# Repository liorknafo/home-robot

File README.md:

# R1 home robot

A round (Ø 318 mm, 135.15 mm tall) differential-drive home robot built around an NVIDIA Jetson Nano, together with the Unreal
simulator and the Python autonomy stack it is developed against.

| Folder | What's in it |
|---|---|
| [`home-robot-r1/`](home-robot-r1) | Robot hardware: parametric CAD (CadQuery), printable parts, the 4-layer power & I/O board (KiCad, generated from Python and auto-routed), fab package for JLCPCB, harness and BOM, bring-up guide |
| [`home-robot-sim/`](home-robot-sim) | Unreal Engine 5.8 simulator (a furnished apartment, the robot with its LiDAR, camera, IMU, encoders, bumpers and cliff sensors) and the autonomy controller (LiDAR mapping, camera low-obstacle detection, exploration, go-to) |

Status: work in progress. Nothing has been ordered or printed yet.

## Robot at a glance

- **Compute:** Jetson Nano 4 GB developer kit on standoffs over the motors: B01 (the CAD model) or A02 (same footprint, ports and power).
- **Board:** a 74 × 100 mm 4-layer power & I/O board under the Jetson. It carries:
  - a Raspberry Pi Pico for real-time I/O;
  - two Pololu DRV8874 motor drivers;
  - a GY-521 (MPU-6050) IMU;
  - fuses, a relay and connectors.
- **Sensors:**
  - an LDROBOT LD14 (D200) 2D LiDAR at 127.5 mm;
  - one camera at 80 mm;
  - four downward ToF cliff sensors;
  - a front bumper.
- **Drive:** Pololu 25D 99:1 encoder gearmotors.

## Key documents

**Hardware:**
- [`home-robot-r1/BRINGUP.md`](home-robot-r1/BRINGUP.md): assembly order and first power-up.
  - **J1 pin 1 is GND.**
  - Includes the IMU calibration.
- [`home-robot-r1/pcb/fab/ORDERING.md`](home-robot-r1/pcb/fab/ORDERING.md): exact JLCPCB order settings and a verify-before-ordering checklist.
- [`home-robot-r1/pcb/fab/`](home-robot-r1/pcb/fab): Gerbers, drill files, BOM, placement file, 1:1 PDF and board STEP.
- `home-robot-r1/parts-and-connections.json` and `cable-cut-list.json`: the BOM and the harness.

**Design history:** [`home-robot-sim/docs/superpowers/`](home-robot-sim/docs/superpowers) holds the specs and plans.

## What is not in this repo

- **Manufacturer 3D models:** NVIDIA Jetson Nano, Pololu motor and driver, Raspberry Pi Pico, LDROBOT LD14.
  - Their licences don't clearly allow redistribution, so they are fetched instead.
  - The same goes for the generated meshes that contain their geometry: `cad/assembly-meshes.json`, `cad/home-robot-r1.glb`, `design-review.html`, and the simulator's `Content/RobotData/assembly-meshes.json`.
  - Sources and checksums are in [`home-robot-r1/reference-models/SOURCE.txt`](home-robot-r1/reference-models/SOURCE.txt).
- **Simulator data:** recordings (`Saved/`), build output, caches and benchmark reports.

## Build

1. **Fetch the reference models:** `tools/fetch_reference_models.sh`. The NVIDIA Jetson model needs a manual download; the script prints the steps.
2. **Robot CAD:**
   - Python 3.13 with CadQuery 2.6.1 (`home-robot-r1/cad/requirements.txt`; CadQuery 2.8.0 + cadquery-ocp 7.9.3.1.1 on Python 3.14 also verified).
   - Run `python home-robot-r1/cad/build_robot.py`. It takes about 25 min, and writes the meshes, STEP, print STLs and validation report.
3. **Board (optional):**
   - KiCad 9.0.x (its bundled Python, `$KPY` in the script headers, runs the `pcb/` scripts and `ktest_*` tests): on macOS
     `/Applications/KiCad/KiCad.app/Contents/Frameworks/Python.framework/Versions/Current/bin/python3`, on Windows
     `C:\Program Files\KiCad\9.0\bin\python.exe` (or `%LOCALAPPDATA%\Programs\KiCad\9.0\bin\python.exe` for a per-user install), on
     Linux the system `python3` with the distribution's KiCad 9 packages.
   - Re-routing needs Java 25 and Freerouting 2.4.1 at `home-robot-r1/pcb/tools/freerouting.jar`. It isn't redistributed; download it from the Freerouting releases
     (`pcb/tools.py` pins its sha256, `FREEROUTING_SHA256`).
   - `pcb/tools.py` finds these per OS. Override any of them with `KICAD_CLI`, `KICAD_PYTHON`, `KICAD9_SYMBOL_DIR`, `KICAD9_FOOTPRINT_DIR`,
     `KICAD9_3DMODEL_DIR`, `JAVA` (or `JAVA_HOME`) and `FREEROUTING_JAR`.
   - `pcb/route.py` with no arguments reproduces the committed routing with these versions; it records them in the board's `ROUTED_WITH`.
   - KiCad 9.0.8's `kicad-cli`, on its first `sch erc` run in a fresh config dir, copies KiCad's template `fp-lib-table` into that dir and
     then crashes; every later run passes. So on a fresh install or CI the first `test_erc_has_no_errors` (or `test_schematic.py`) run
     fails: run it again, or first copy `<KiCad>/share/kicad/template/fp-lib-table` (macOS:
     `/Applications/KiCad/KiCad.app/Contents/SharedSupport/template/fp-lib-table`) to `fp-lib-table` in the 9.0 config dir
     (`%APPDATA%\kicad\9.0`, `~/Library/Preferences/kicad/9.0`, `~/.config/kicad/9.0`).
4. **Simulator:**
   - Unreal Engine 5.8 (macOS): build with `home-robot-sim/Scripts/build.command`.
   - Sync the robot data: `python home-robot-sim/Scripts/sync_robot_data.py`. It reads `../home-robot-r1/cad` and copies the robot meshes and parameters.
   - Launch with `Scripts/launch.command house polished`.
   - Start the autonomy service: `Scripts/start-autonomy.command`, then open http://127.0.0.1:8771/autonomy.html.
   - Python deps: `home-robot-sim/controller/requirements.txt`.
   - **Windows:** every `.command` script has a `.cmd` twin in `home-robot-sim/Scripts` (`build.cmd`, `launch.cmd house polished`,
     `start-autonomy.cmd`, `run-tests.cmd`, `drive-house.cmd`, `drive-square.cmd`, `process-cameras.cmd`).
     - One command runs everything: `.\home-robot-sim\Scripts\launch.cmd house polished` starts the simulator plus, in
       minimized windows, the autonomy service and object detection, then open http://127.0.0.1:8771/autonomy.html.
       Every launcher first stops its own earlier runs, so rerunning it never leaves duplicates (`NO_AUTONOMY=1` /
       `NO_VISION=1` skip a part).
     - Needs Unreal Engine 5.8 from the Epic Games Launcher (the scripts find it on any drive through the launcher's install record,
       or set `UE_ROOT`) and
       Visual Studio 2022 17.14+ with the "Game development with C++" workload, MSVC 14.38+ and Windows SDK 10.0.22621+.
     - The scripts make `home-robot-sim\.venv` on first use and run Python in UTF-8 mode (`PYTHONUTF8=1`). Set it yourself when you
       run the Python tools directly, e.g. the CAD build, or they read the UTF-8 sources in the ANSI code page.
     - `tools/fetch_reference_models.sh` runs in Git Bash. Verified with Python 3.13 + CadQuery 2.6.1 for the CAD build.
   - **Live object recognition (display only):** started by `launch.cmd`, or alone with `start-vision.cmd`. It runs
     YOLO26n-seg on each robot camera frame on the PC's NVIDIA GPU and shows boxes + masks under the dashboard's camera
     image. By default it runs a TensorRT engine for this PC's GPU, built on the fly the first time (about 1-2 minutes,
     `vision/ensure_engine.py`; the file name records the GPU and TensorRT version, so a new GPU or TensorRT gets a fresh
     build). It falls back to PyTorch when TensorRT is unavailable, or with `NO_TRT=1`.
     `start-vision.cmd --model <weights or .engine>` picks the model: any Ultralytics name (e.g. `yolo11n-seg.pt`), or
     `yolov12n-seg.pt`, fetched from the YOLOv12 authors' release and loaded through `vision/yolov12_compat.py`
     (Ultralytics publishes no YOLO12 segmentation weights). The robot does not act on these detections.
     The pipeline is PyTorch end to end (`vision/yoloseg`, no OpenCV) and is the same one the robot runs.
   - **On the Jetson Nano (TensorRT):** [`home-robot-sim/jetson/JETSON.md`](home-robot-sim/jetson/JETSON.md) goes step by step
     from the ONNX export on the PC to the FP16 engine and the live camera view on the Nano.
5. **Tests:**
   - Simulator: `cd home-robot-sim && python -m unittest discover -s tests`, plus `tests/scenarios_round.py`.
   - Robot pure tests: `cd home-robot-r1 && python -m unittest discover -s pcb/tests -t .` (or `python -m pytest pcb/tests`;
     they include the CAD review-page checks). The tests that need KiCad skip when it isn't found; `R1_REQUIRE_KICAD=1` makes them run (and fail).
   - Board tests in KiCad's Python: `cd home-robot-r1 && $KPY -m unittest pcb.tests.ktest_pcb pcb.tests.ktest_power pcb.tests.ktest_route`.

## Licence

MIT (see [`LICENSE`](LICENSE)) for everything in this repo: software, CAD, board design and documents. The manufacturer 3D models fetched by `tools/fetch_reference_models.sh` keep their own terms and are not part of this repo.

## Repository maintenance

This repo is a published snapshot of two working folders that live next to it. To refresh and push it:
`tools/sync.sh && git add -A && git commit -m "…" && git push`.

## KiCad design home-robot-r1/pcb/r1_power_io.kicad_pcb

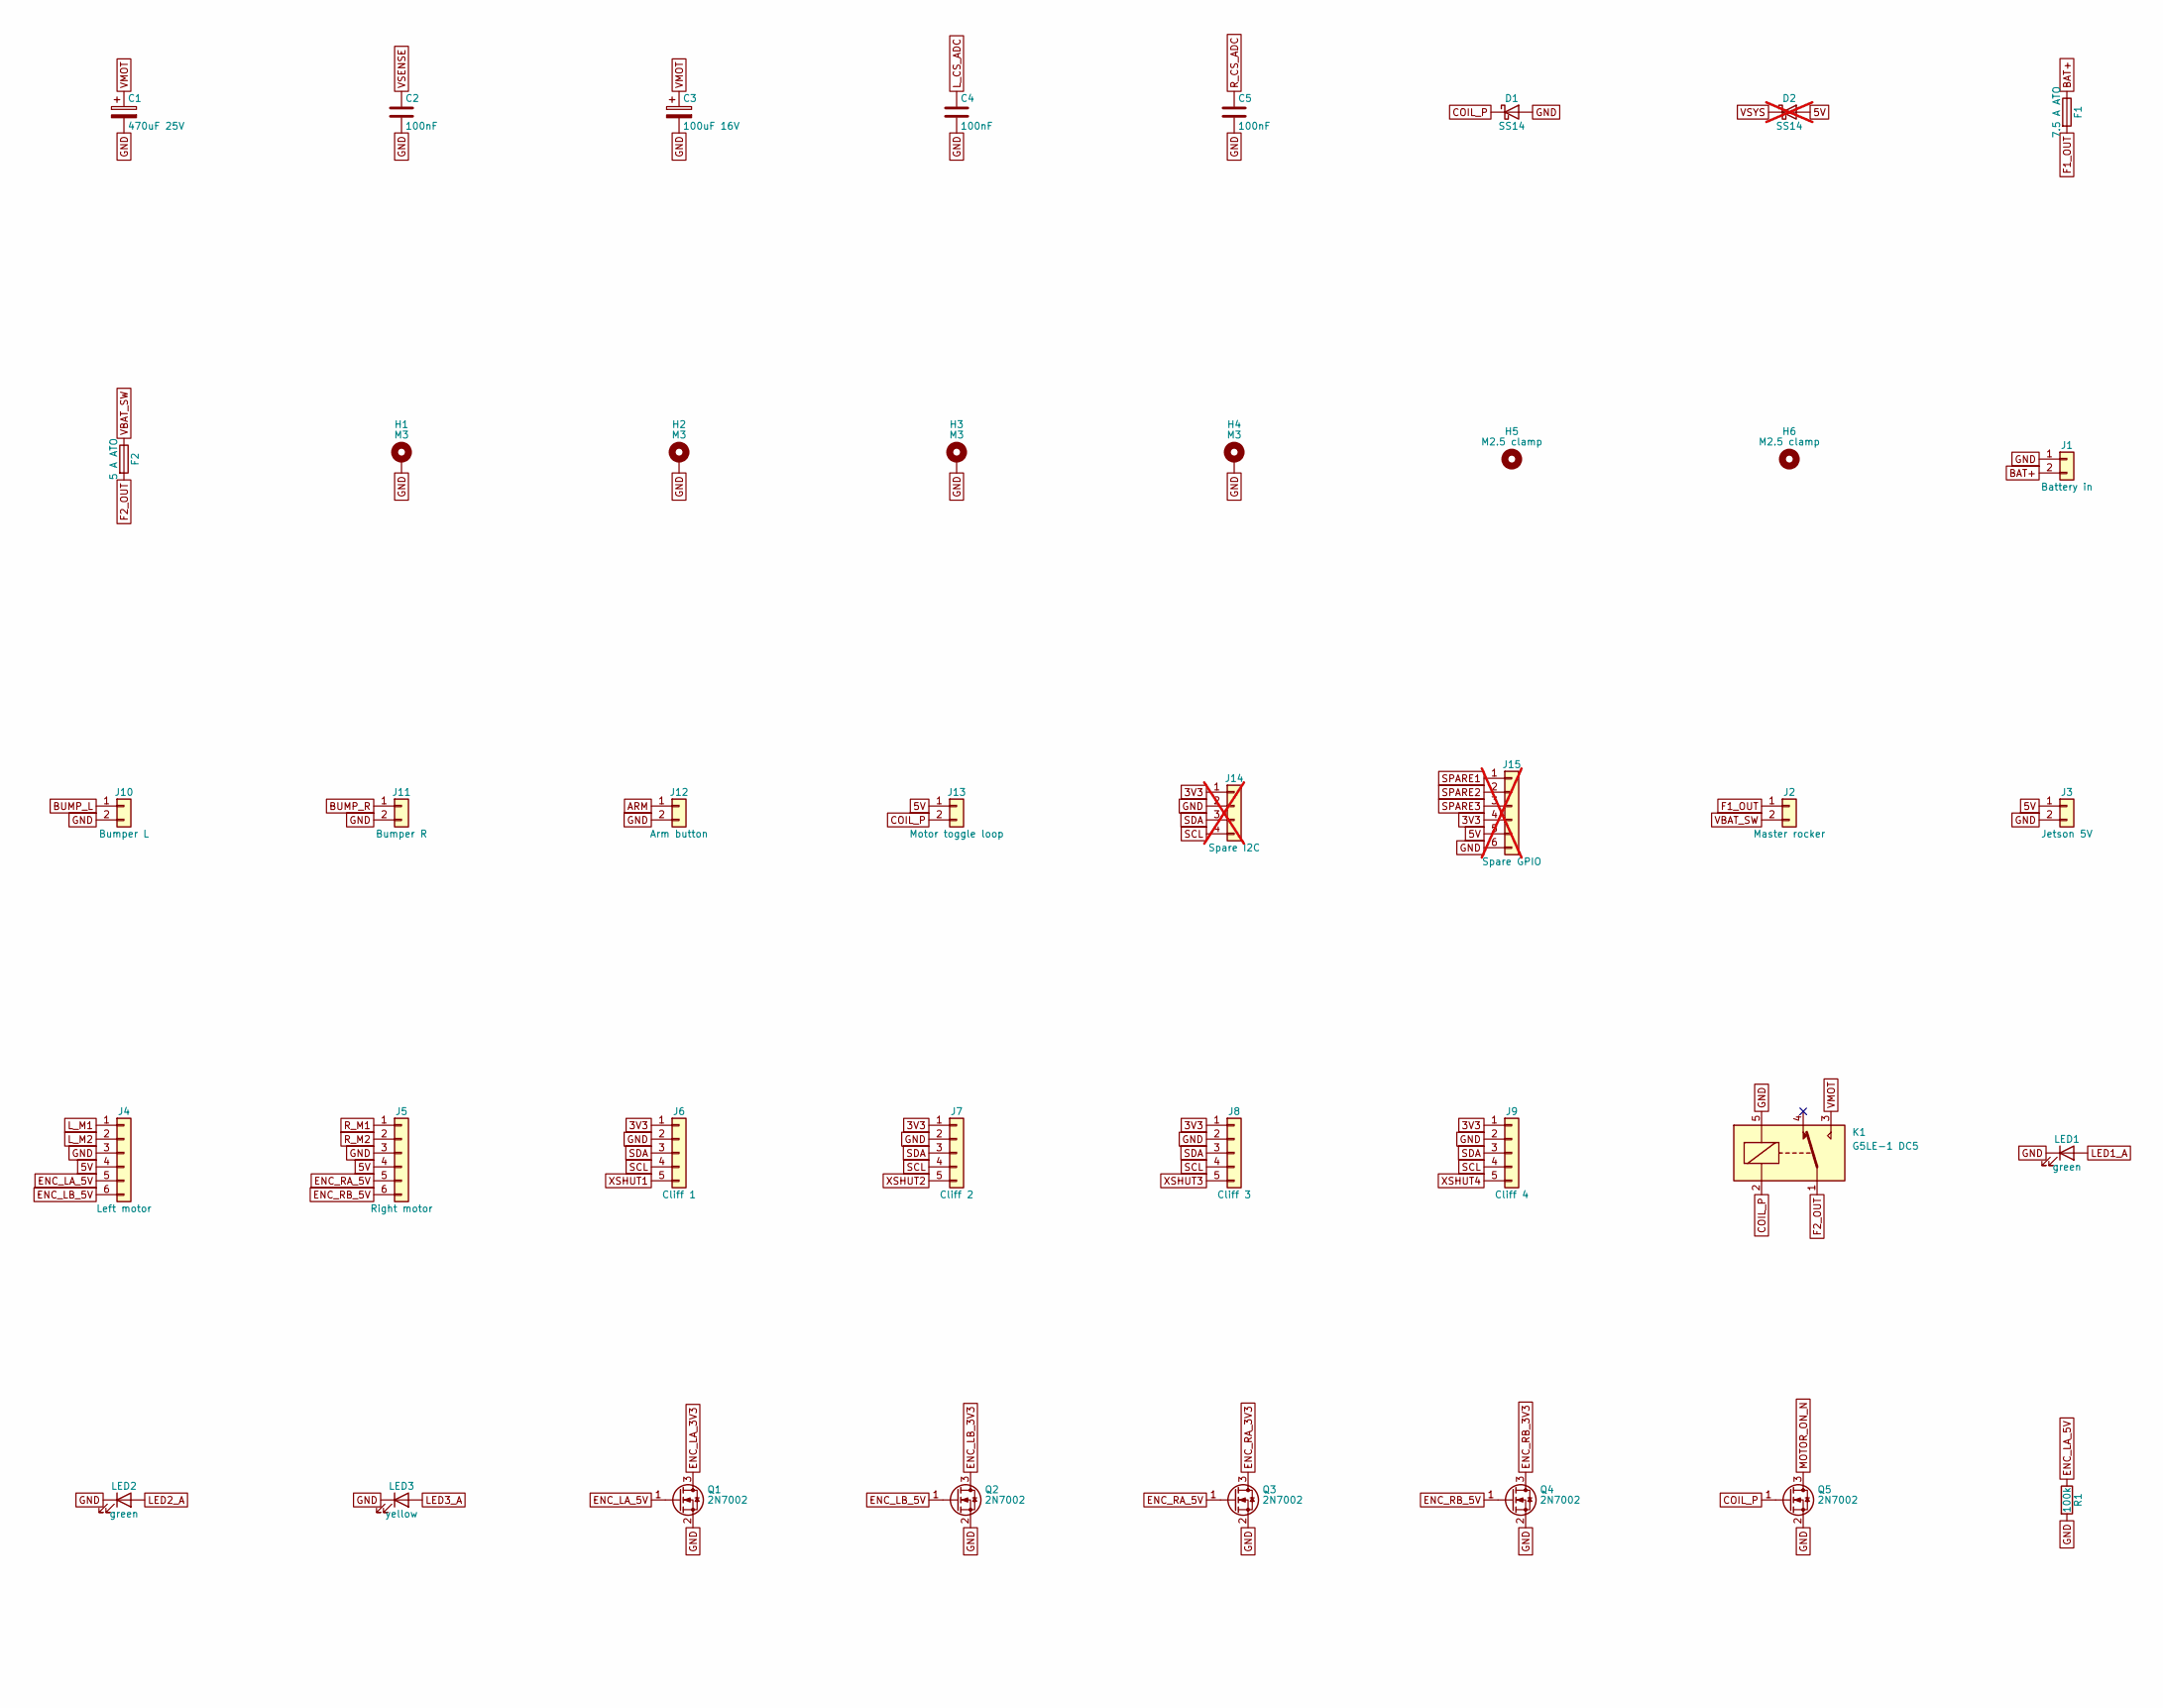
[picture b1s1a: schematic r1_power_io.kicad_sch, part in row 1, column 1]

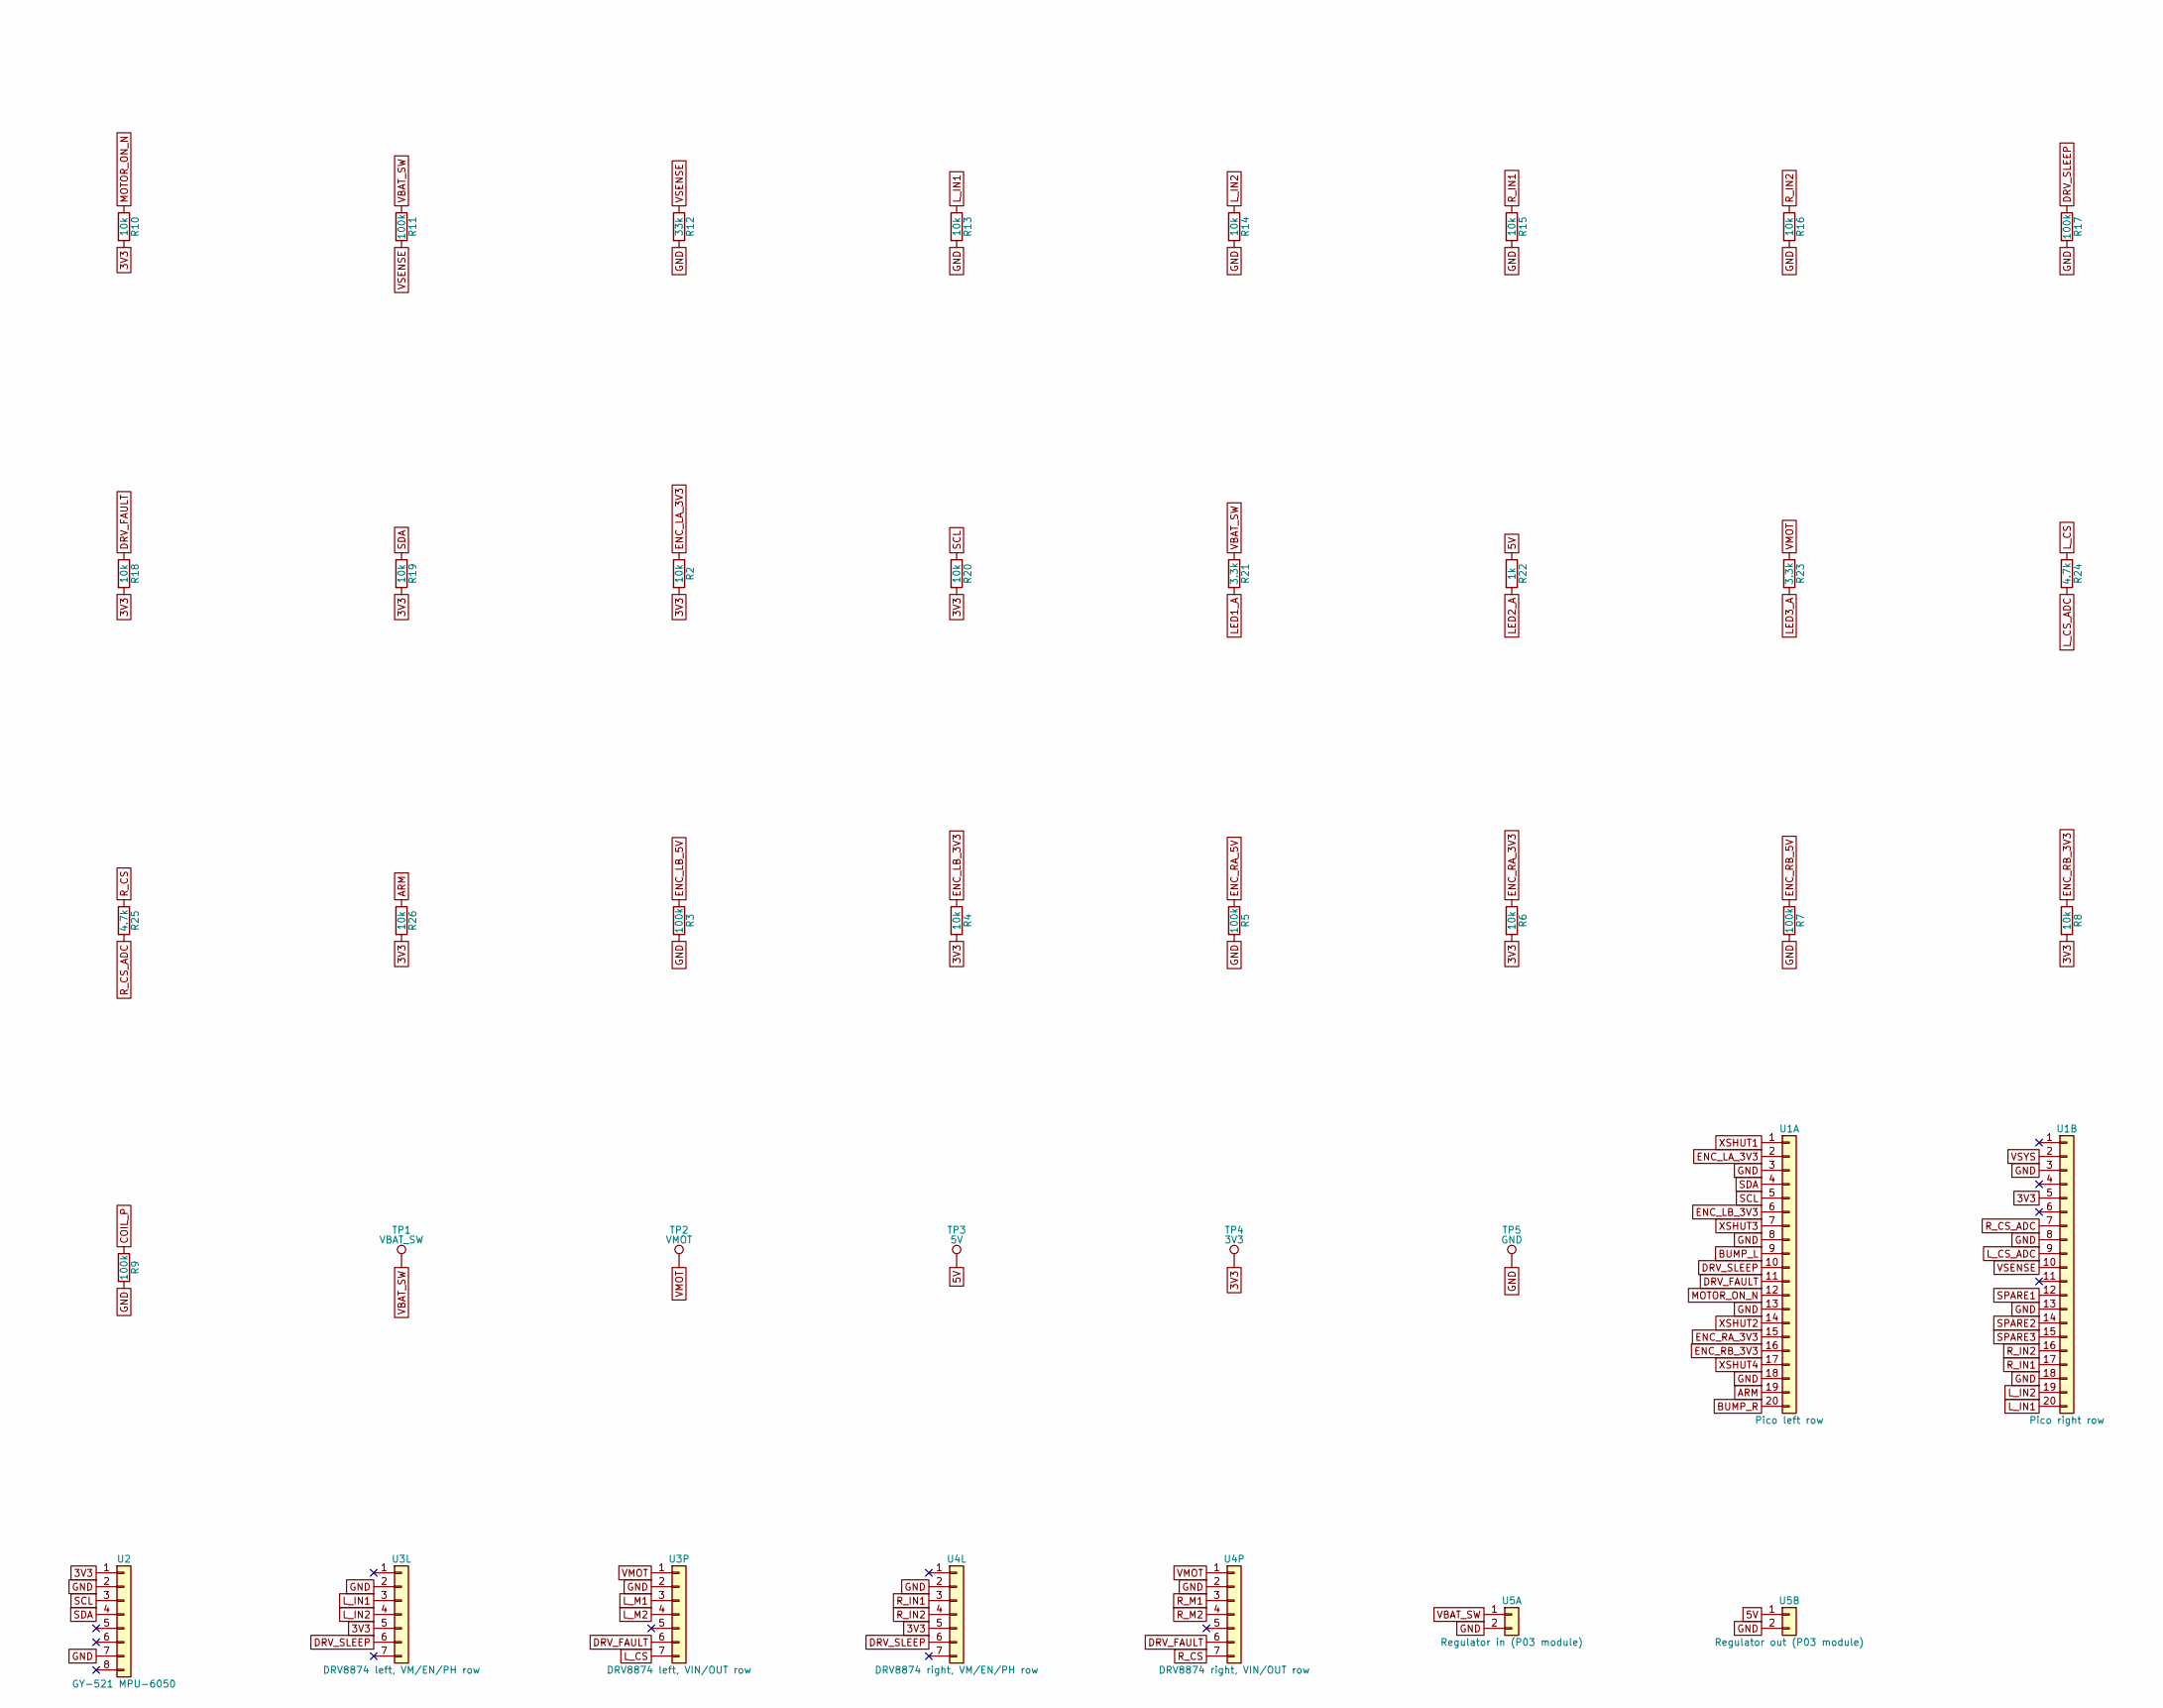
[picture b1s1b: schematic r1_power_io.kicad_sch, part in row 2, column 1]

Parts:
C1: 470uF 25V; CP_Radial_D10.0mm_P5.00mm
C2, C4, C5: 100nF; C_0805_2012Metric
C3: 100uF 16V; CP_Elec_6.3x5.8
D1: SS14; D_SMA
D2: SS14; D_SMA; not fitted
F1: 7.5 A ATO; FuseHolder_Blade_ATO_Littelfuse_FLR_178.6165
F2: 5 A ATO; FuseHolder_Blade_ATO_Littelfuse_FLR_178.6165
H1, H2, H3, H4: M3; MountingHole_3.2mm_M3_Pad_Via
H5, H6: M2.5 clamp; MountingHole_3mm
J1: Battery in; AMASS_XT30UPB-M_1x02_P5.0mm_Vertical
J2: Master rocker; JST_VH_B2P-VH_1x02_P3.96mm_Vertical
J3: Jetson 5V; Molex_Micro-Fit_3.0_43650-0200_1x02_P3.00mm_Horizontal
J4: Left motor; PinHeader_1x06_P2.54mm_Horizontal
J5: Right motor; PinHeader_1x06_P2.54mm_Horizontal
J6: Cliff 1; JST_XH_B5B-XH-A_1x05_P2.50mm_Vertical
J7: Cliff 2; JST_XH_B5B-XH-A_1x05_P2.50mm_Vertical
J8: Cliff 3; JST_XH_B5B-XH-A_1x05_P2.50mm_Vertical
J9: Cliff 4; JST_XH_B5B-XH-A_1x05_P2.50mm_Vertical
J10: Bumper L; JST_XH_B2B-XH-A_1x02_P2.50mm_Vertical
J11: Bumper R; JST_XH_B2B-XH-A_1x02_P2.50mm_Vertical
J12: Arm button; JST_XH_B2B-XH-A_1x02_P2.50mm_Vertical
J13: Motor toggle loop; JST_XH_B2B-XH-A_1x02_P2.50mm_Vertical
J14: Spare I2C; PinHeader_1x04_P2.54mm_Vertical; not fitted
J15: Spare GPIO; PinHeader_1x06_P2.54mm_Vertical; not fitted
K1: G5LE-1 DC5; Relay_SPDT_Omron-G5LE-1
LED1, LED2: green; LED_0805_2012Metric
LED3: yellow; LED_0805_2012Metric
Q1, Q2, Q3, Q4, Q5: 2N7002; SOT-23
R1, R3, R5, R7, R9, R11, R17: 100k; R_0805_2012Metric
R2, R4, R6, R8, R10, R13, R14, R15, R16, R18, R19, R20, R26: 10k; R_0805_2012Metric
R12: 33k; R_0805_2012Metric
R21, R23: 3.3k; R_0805_2012Metric
R22: 1k; R_0805_2012Metric
R24, R25: 4.7k; R_0805_2012Metric
TP1: VBAT_SW; TestPoint_Pad_D2.0mm
TP2: VMOT; TestPoint_Pad_D2.0mm
TP3: 5V; TestPoint_Pad_D2.0mm
TP4: 3V3; TestPoint_Pad_D2.0mm
TP5: GND; TestPoint_Pad_D2.0mm
U1A: Pico left row; PinSocket_1x20_P2.54mm_Vertical
U1B: Pico right row; PinSocket_1x20_P2.54mm_Vertical
U2: GY-521 MPU-6050; PinSocket_1x08_P2.54mm_Vertical
U3L: DRV8874 left, VM/EN/PH row; PinSocket_1x07_P2.54mm_Vertical
U3P: DRV8874 left, VIN/OUT row; PinSocket_1x07_P2.54mm_Vertical
U4L: DRV8874 right, VM/EN/PH row; PinSocket_1x07_P2.54mm_Vertical
U4P: DRV8874 right, VIN/OUT row; PinSocket_1x07_P2.54mm_Vertical
U5A: Regulator in (P03 module); TerminalBlock_Phoenix_MKDS-1,5-2-5.08_1x02_P5.08mm_Horizont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
U5B: Regulator out (P03 module); TerminalBlock_Phoenix_MKDS-1,5-2-5.08_1x02_P5.08mm_Horizont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

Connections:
3V3: J6.1, J7.1, J8.1, J9.1, J14.1, J15.4, R2.2, R4.2, R6.2, R8.2, R10.2, R18.2, R19.2, R20.2, R26.2, TP4.1, U1B.5, U2.1, U3L.5, U4L.5
5V: D2.2 (A), J3.1, J4.4, J5.4, J13.1, J15.5, R22.1, TP3.1, U5B.1
ARM: J12.1, R26.1, U1A.19
BAT+: F1.1, J1.2
BUMP_L: J10.1, U1A.9
BUMP_R: J11.1, U1A.20
COIL_P: D1.1 (K), J13.2, K1.2, Q5.1 (G), R9.1
DRV_FAULT: R18.1, U1A.11, U3P.6, U4P.6
DRV_SLEEP: R17.1, U1A.10, U3L.6, U4L.6
ENC_LA_3V3: Q1.3 (D), R2.1, U1A.2
ENC_LA_5V: J4.5, Q1.1 (G), R1.1
ENC_LB_3V3: Q2.3 (D), R4.1, U1A.6
ENC_LB_5V: J4.6, Q2.1 (G), R3.1
ENC_RA_3V3: Q3.3 (D), R6.1, U1A.15
ENC_RA_5V: J5.5, Q3.1 (G), R5.1
ENC_RB_3V3: Q4.3 (D), R8.1, U1A.16
ENC_RB_5V: J5.6, Q4.1 (G), R7.1
F1_OUT: F1.2, J2.1
F2_OUT: F2.2, K1.1
GND: C1.2, C2.2, C3.2, C4.2, C5.2, D1.2 (A), H1.1, H2.1, H3.1, H4.1, J1.1, J3.2, J4.3, J5.3, J6.2, J7.2, J8.2, J9.2, J10.2, J11.2, J12.2, J14.2, J15.6, K1.5, LED1.1 (K), LED2.1 (K), LED3.1 (K), Q1.2 (S), Q2.2 (S), Q3.2 (S), Q4.2 (S), Q5.2 (S), R1.2, R3.2, R5.2, R7.2, R9.2, R12.2, R13.2, R14.2, R15.2, R16.2, R17.2, TP5.1, U1A.3, U1A.8, U1A.13, U1A.18, U1B.3, U1B.8, U1B.13, U1B.18, U2.2, U2.7, U3L.2, U3P.2, U4L.2, U4P.2, U5A.2, U5B.2
LED1_A: LED1.2 (A), R21.2
LED2_A: LED2.2 (A), R22.2
LED3_A: LED3.2 (A), R23.2
L_CS: R24.1, U3P.7
L_CS_ADC: C4.1, R24.2, U1B.9
L_IN1: R13.1, U1B.20, U3L.3
L_IN2: R14.1, U1B.19, U3L.4
L_M1: J4.1, U3P.3
L_M2: J4.2, U3P.4
MOTOR_ON_N: Q5.3 (D), R10.1, U1A.12
R_CS: R25.1, U4P.7
R_CS_ADC: C5.1, R25.2, U1B.7
R_IN1: R15.1, U1B.17, U4L.3
R_IN2: R16.1, U1B.16, U4L.4
R_M1: J5.1, U4P.3
R_M2: J5.2, U4P.4
SCL: J6.4, J7.4, J8.4, J9.4, J14.4, R20.1, U1A.5, U2.3
SDA: J6.3, J7.3, J8.3, J9.3, J14.3, R19.1, U1A.4, U2.4
SPARE1: J15.1, U1B.12
SPARE2: J15.2, U1B.14
SPARE3: J15.3, U1B.15
VBAT_SW: F2.1, J2.2, R11.1, R21.1, TP1.1, U5A.1
VMOT: C1.1, C3.1, K1.3, R23.1, TP2.1, U3P.1, U4P.1
VSENSE: C2.1, R11.2, R12.1, U1B.10
VSYS: D2.1 (K), U1B.2
XSHUT1: J6.5, U1A.1
XSHUT2: J7.5, U1A.14
XSHUT3: J8.5, U1A.7
XSHUT4: J9.5, U1A.17

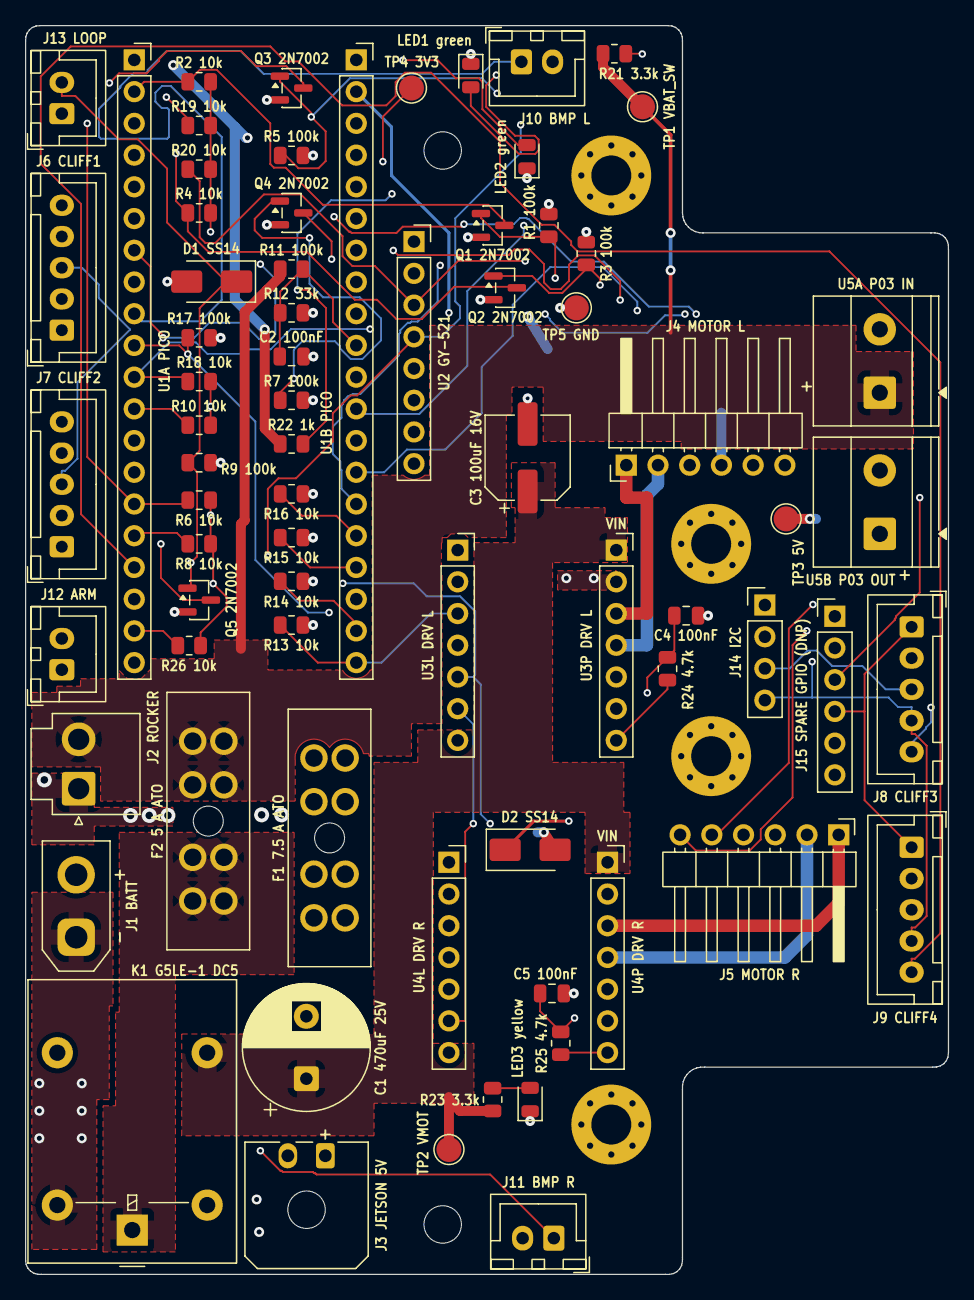
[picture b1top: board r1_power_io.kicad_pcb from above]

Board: 4 copper layers, 73.9 x 100.0 mm, 79 parts (0 on the bottom side), 49 nets.

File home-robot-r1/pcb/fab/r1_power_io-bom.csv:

Refs,Qty,Fit,Value,MPN,Footprint,Mount,Notes
C2 C4 C5,3,yes,100nF,Samsung CL21B104KBCNNNC (100 nF 50 V X7R 0805; verify before ordering),Capacitor_SMD:C_0805_2012Metric,SMD top (reflow),
C3,1,yes,100uF 16V,"Panasonic EEE-FK1C101P (FK, low ESR, 6.3 x 5.8 mm; verify before ordering)",Capacitor_SMD:CP_Elec_6.3x5.8,SMD top (reflow),"polarised: + on silk; under the IMU module (5.8 mm can, PB16 / PB20)"
D1,1,yes,SS14,Vishay SS14-E3/61T (SMA 40 V 1 A Schottky; verify before ordering),Diode_SMD:D_SMA,SMD top (reflow),cathode mark on silk
LED1 LED2,2,yes,green,Lite-On LTST-C171GKT (green 0805; verify before ordering),LED_SMD:LED_0805_2012Metric,SMD top (reflow),cathode mark on silk
LED3,1,yes,yellow,Lite-On LTST-C171YKT (yellow 0805; verify before ordering),LED_SMD:LED_0805_2012Metric,SMD top (reflow),cathode mark on silk
Q1 Q2 Q3 Q4 Q5,5,yes,2N7002,"Nexperia 2N7002,215",Package_TO_SOT_SMD:SOT-23,SMD top (reflow),
R1 R3 R5 R7 R9 R11 R17,7,yes,100k,"Yageo RC0805FR-07100KL (0805, 1 %, 0.125 W thick film; verify before ordering)",Resistor_SMD:R_0805_2012Metric,SMD top (reflow),
R2 R4 R6 R8 R10 R13 R14 R15 R16 R18 R19 R20 R26,13,yes,10k,"Yageo RC0805FR-0710KL (0805, 1 %, 0.125 W thick film; verify before ordering)",Resistor_SMD:R_0805_2012Metric,SMD top (reflow),
R12,1,yes,33k,"Yageo RC0805FR-0733KL (0805, 1 %, 0.125 W thick film; verify before ordering)",Resistor_SMD:R_0805_2012Metric,SMD top (reflow),
R21 R23,2,yes,3.3k,"Yageo RC0805FR-073K3L (0805, 1 %, 0.125 W thick film; verify before ordering)",Resistor_SMD:R_0805_2012Metric,SMD top (reflow),
R22,1,yes,1k,"Yageo RC0805FR-071KL (0805, 1 %, 0.125 W thick film; verify before ordering)",Resistor_SMD:R_0805_2012Metric,SMD top (reflow),
R24 R25,2,yes,4.7k,"Yageo RC0805FR-074K7L (0805, 1 %, 0.125 W thick film; verify before ordering)",Resistor_SMD:R_0805_2012Metric,SMD top (reflow),
C1,1,yes,470uF 25V,Panasonic EEU-FR1E471,Capacitor_THT:CP_Radial_D10.0mm_P5.00mm,THT (iron),polarised: + on silk
F1 F2,2,yes,ATO fuse holder (FLR),Littelfuse 178.6165.0001,Fuse:FuseHolder_Blade_ATO_Littelfuse_FLR_178.6165,THT (iron),"fuse holder only (the fuses are the plug-in rows: 7.5 A ATO in F1, 5 A ATO in F2); the KiCad footprint gives PCB <= 1.5 mm for its snap lock, this board is 1.6 mm: hold it flat and solder all 8 pins"
J1,1,yes,Battery in,"AMASS XT30UPB-M (XT30 vertical PCB male, 2-pin, 15 A continuous; LCSC C428721; verify before ordering)",Connector_AMASS:AMASS_XT30UPB-M_1x02_P5.0mm_Vertical,THT (iron),"battery: pin 1 = GND, pin 2 = BAT+ (PB20; silk - / +): the battery lead GND in cavity 1"
J2,1,yes,Master rocker,JST B2P-VH(LF)(SN),Connector_JST:JST_VH_B2P-VH_1x02_P3.96mm_Vertical,THT (iron),
J3,1,yes,Jetson 5V,"Molex 43650-0200 (Micro-Fit 3.0 1x2 right-angle THT header with peg, 8.5 A/circuit on 18 AWG; verify before ordering)",Connector_Molex:Molex_Micro-Fit_3.0_43650-0200_1x02_P3.00mm_Horizontal,THT (iron),
J4 J5,2,yes,Left motor / Right motor,Amphenol 68016-106HLF (1x6 2.54 mm right-angle pin header; verify before ordering),Connector_PinHeader_2.54mm:PinHeader_1x06_P2.54mm_Horizontal,THT (iron),right-angle: the C18 pigtail socket lies on the board (PB25)
J6 J7 J8 J9,4,yes,Cliff 1 / Cliff 2 / Cliff 3 / Cliff 4,JST B5B-XH-A(LF)(SN),Connector_JST:JST_XH_B5B-XH-A_1x05_P2.50mm_Vertical,THT (iron),
J10 J11 J12 J13,4,yes,Bumper L / Bumper R / Arm button / Motor toggle loop,JST B2B-XH-A(LF)(SN),Connector_JST:JST_XH_B2B-XH-A_1x02_P2.50mm_Vertical,THT (iron),
K1,1,yes,G5LE-1 DC5,Omron G5LE-1 DC5,Relay_THT:Relay_SPDT_Omron-G5LE-1,THT (iron),
U1A U1B,2,yes,Pico left row / Pico right row,"Sullins PPTC201LFBN-RC (1x20 2.54 mm female socket, 8.5 mm body; verify before ordering)",Connector_PinSocket_2.54mm:PinSocket_1x20_P2.54mm_Vertical,THT (iron),
U2,1,yes,GY-521 MPU-6050,"Sullins PPTC081LFBN-RC (1x8 2.54 mm female socket, 8.5 mm body; verify before ordering)",Connector_PinSocket_2.54mm:PinSocket_1x08_P2.54mm_Vertical,THT (iron),
U3L U3P U4L U4P,4,yes,"DRV8874 left, VM/EN/PH row / DRV8874 left, VIN/OUT row / DRV8874 right, VM/EN/PH row / DRV8874 right, VIN/OUT row","Sullins PPTC071LFBN-RC (1x7 2.54 mm female socket, 8.5 mm body; verify before ordering)",Connector_PinSocket_2.54mm:PinSocket_1x07_P2.54mm_Vertical,THT (iron),
U5A U5B,2,yes,Regulator in (P03 module) / Regulator out (P03 module),"Phoenix Contact 1715721 (MKDS 1,5/ 2-5,08; verify before ordering)","TerminalBlock_Phoenix:TerminalBlock_Phoenix_MKDS-1,5-2-5.08_1x02_P5.08mm_Horizontal",THT (iron),
D2,1,DNP,SS14,Vishay SS14-E3/61T (SMA 40 V 1 A Schottky; verify before ordering),Diode_SMD:D_SMA,SMD top (reflow),"DNP (LIO-226): 5V to the Pico's VSYS, fit it to run the Pico and 3V3 without the Jetson USB (BRINGUP.md section 4 item 2); under the DRV_R carrier; cathode mark on silk"
J14,1,DNP,Spare I2C,,Connector_PinHeader_2.54mm:PinHeader_1x04_P2.54mm_Vertical,THT (iron),DNP spare pad row (PB8); a bare 1x4 2.54 mm header may be fitted later (<= 8.5 mm tall)
J15,1,DNP,Spare GPIO,,Connector_PinHeader_2.54mm:PinHeader_1x06_P2.54mm_Vertical,THT (iron),DNP spare pad row (PB8); a bare 1x6 2.54 mm header may be fitted later (<= 8.5 mm tall)
TP1 TP2 TP3 TP4 TP5,5,no part,VBAT_SW / VMOT / 5V / 3V3 / GND,,TestPoint:TestPoint_Pad_D2.0mm,SMD top (reflow),"bare copper test pad, no part"
H1 H2 H3 H4,4,no part,M3,,MountingHole:MountingHole_3.2mm_M3_Pad_Via,THT (iron),"plated M3 mounting hole (GND ring), no part"
H5 H6,2,no part,M2.5 clamp,,MountingHole:MountingHole_3mm,THT (iron),"M2.5 clamp hole (NPTH, PB3), no part"
,1,plug-in,"Raspberry Pi Pico (RP2040), owned (E02), with 2.54 mm male headers soldered on by the user","Raspberry Pi SC0915 (bare Pico, no headers; owned, E02; solder two 1x20 male strips before it goes in the sockets)",,plugs in,"into U1A, U1B"
,2,plug-in,DRV8874 single brushed DC motor driver carrier,Pololu 4035,,plugs in,"into U3L, U3P, U4L, U4P"
,1,plug-in,GY-521 MPU-6050 IMU module,"HiLetgo GY-521 (owned, E03)",,plugs in,into U2
,1,plug-in,"P03 adjustable 5 V buck module, leads to the terminals",P03 (owned; set 5.1 V on the bench first),,plugs in,"into U5A, U5B"
,1,plug-in,ATO blade fuse 7.5 A (main),Littelfuse 0287007.PXCN (ATO 7.5 A; verify before ordering),,plugs in,into F1
,1,plug-in,ATO blade fuse 5 A (motor branch),Littelfuse 0287005.PXCN (ATO 5 A; verify before ordering),,plugs in,into F2

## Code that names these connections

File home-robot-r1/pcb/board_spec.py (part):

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REG_B_PINS = {'EN': 1, 'VIN': 2, 'GND': 3, 'GND2': 4, 'VOUT': 5}   # name -> pin number (pololu-2851.txt)
# Vendor record only: the D24V50F5 socket (U5C) is not fitted on the strip board (L5); the user's P03 on U5A / U5B is the regulator.
RELAY_SYM = 'Relay:G5LE-1'         # Omron G5LE-1 (pin map from the Omron datasheet, omron-g5le-1.txt)
RELAY_PINS = {'COIL_P': '2', 'COIL_N': '5', 'COM': '1', 'NO': '3', 'NC': '4'}   # coil is unpolarised: P/N only places the flyback diode
# KiCad 9's stock Fuse library has a real, buyable through-hole ATO holder (Littelfuse FLR 178.6165.0001, 30 A, 80 V; 4 solder pins
# per contact, so pads are numbered 1,1,1,1,2,2,2,2): no custom library.
FUSE_FP = 'Fuse:FuseHolder_Blade_ATO_Littelfuse_FLR_178.6165'
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# J1 pinout changed (PB20): pin 1 = GND, pin 2 = BAT+. Pin 1 is the south pin (v 73.0 since B12a's XT30; was 71.57), beside the free F.Cu
# west strip, K1.5 and the main B.Cu GND fill, so the battery return leaves on outer-layer copper; pin 2 (v 68.0) faces J2 / F1, next to
# BAT+'s fuse. B12a: the XT30UPB-M footprint's own '-' / '+' pads are pins 1 / 2, so the pinout holds. Until bay
# B6 it was the other way round (pin 1 BAT+), which boxed the return pin in between BAT+ and F1_OUT. The battery lead (B9 harness) and the
# sim / BRINGUP docs (B10) follow this table; the silk carries '+' / '-' at the pins (PIN_MARKS).
J1_PINOUT = {'1': 'GND', '2': 'BAT+'}
J1_GND_PIN, J1_BAT_PIN = ('J1', '1'), ('J1', '2')
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    n = {}
    def add(net, *pins): n.setdefault(net, []).extend(pins)
    for r, (v, a, b) in RES.items(): add(a, (r, '1')); add(b, (r, '2'))
    add('BAT+', J1_BAT_PIN, ('F1', '1')); add('F1_OUT', ('F1', '2'), ('J2', '1'))
    add('VBAT_SW', ('J2', '2'), ('F2', '1'), ('U5A', '1'), ('TP1', '1'))
    add('F2_OUT', ('F2', '2'), ('K1', RELAY_PINS['COM']))
    add('VMOT', ('K1', RELAY_PINS['NO']), ('C1', '1'), ('C3', '1'), drv('L', 'VIN'), drv('R', 'VIN'), ('TP2', '1'))
    add('5V', ('U5B', '1'), ('J3', '1'), ('J4', '4'), ('J5', '4'), ('J13', '1'), ('J15', '5'), ('TP3', '1'), dio('D2', 'A'))
    add('VSYS', dio('D2', 'K'), pico('VSYS'))                                       # LIO-226: D2 (DNP) 5V -> VSYS
    add('3V3', pico('3V3_OUT'), imu('VCC'), *[(f'J{6 + i}', '1') for i in range(4)], ('J14', '1'), ('J15', '4'), ('TP4', '1'))
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           *[q(i, 'S') for i in range(1, 6)], *[(f'LED{i}', '1') for i in range(1, 4)]]
    if DRV_PMODE_NET == 'GND': gnd += [drv('L', 'PMODE'), drv('R', 'PMODE')]
    add('GND', *gnd)
    add('COIL_P', ('J13', '2'), ('K1', RELAY_PINS['COIL_P']), dio('D1', 'K'), q(5, 'G'))   # D1 cathode on coil+, anode on GND
    for side, j in (('L', 'J4'), ('R', 'J5')):
        add(f'{side}_M1', (j, '1'), drv(side, 'OUT1')); add(f'{side}_M2', (j, '2'), drv(side, 'OUT2'))
        add(f'{side}_CS', drv(side, 'CS')); add(f'{side}_IN1', drv(side, 'IN1')); add(f'{side}_IN2', drv(side, 'IN2'))
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# KiCad custom DRC rules, written to r1_power_io.kicad_dru by make_schematic.py. The Motor class's 1.0 mm (R16) cannot hold between a
# motor pin and its neighbours in the same 2.54 mm header / carrier row (1.7 mm pads, 0.84 mm apart: J4, J5, U3P, U4P), so pad pairs
# within one footprint keep the class's former 0.3 mm; every track, via and zone keeps 1.0 mm from motor copper.
# Ruling PB21 (B6 fix 2): U3P.2 (DRV_L GND) can take one relief spoke per outer layer only - U3P.1 (VMOT) north, U3P.3 (L_M1, Motor
# 1.0 mm) south and the L_M1 track (u 49.85, held west of H3's washer) east leave the west side alone - so its GND patch joins it with one
# F.Cu spoke and the B.Cu GND fill with one B.Cu spoke, below KiCad's default of 2 (starved_thermal). The rule accepts 1 for that pad
# alone; ktest_power proves those spokes' current (pad metric) and ktest_pcb that no other pad is excused.
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POWER_TRUNK = {   # pads the high-current path must join with >= 3 mm zone copper on every trunk layer (zone_check; B6 sizes it by IPC-2221)
    'BAT+': [J1_BAT_PIN, ('F1', '1')],                  # bay B4: the battery-side nets are zone trunks too (PB20: J1.2)
    'F1_OUT': [('F1', '2'), ('J2', '1')],
    'F2_OUT': [('F2', '2'), ('K1', RELAY_PINS['COM'])],
    'VBAT_SW': [('J2', '2'), ('F2', '1'), ('U5A', '1')],
    'VMOT': [('K1', RELAY_PINS['NO']), ('C1', '1'), drv('L', 'VIN'), drv('R', 'VIN')],
    '5V': [('U5B', '1'), ('J3', '1')],
    'GND': [J1_GND_PIN, ('J3', '2'), ('U5A', '2'), ('U5B', '2'), ('C1', '2'), drv('L', 'GND'), drv('R', 'GND')],
}
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# with no trunk zone is fed. Sources marked "verify" are manufacturer figures not in the repo (quoted from memory, check before B9).
TAP_NETS = ('VBAT_SW', 'VMOT', '5V', '3V3', 'VSYS')
TAP_SOURCE = {'3V3': pico('3V3_OUT'),       # the Pico's 3.3 V regulator: 300 mA for external loads (Pico datasheet, verify)
              'VSYS': dio('D2', 'K')}       # LIO-232: VSYS is fed through the DNP D2 (if fitted); its load is the Pico's VSYS pin
VBAT_MAX, V5_MAX, LED_VF_MIN = 8.7, 5.25, 1.8   # spec 2026-10-04 s.6: VBAT_SW 6.0-8.7 V; the P03 5 V set +5 %; 0805 LED V_F, low end
ENC_SUPPLY_A = 0.010    # Pololu 4867 (25D, 48 CPR encoder): its Hall sensors draw at most 10 mA (Pololu product page, verify)
RELAY_COIL_A = V5_MAX / 63.0   # Omron G5LE-1 DC5 coil: 63 ohm, 79.4 mA rated at 5 V (Omron datasheet, verify) -> 83 mA at 5.25 V
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    ('J13', '1'): RELAY_COIL_A,      # the motor toggle loop feeds K1's coil (J13.2 -> COIL_P)
    ('J15', '5'): SPARE_5V_A, ('J14', '1'): SPARE_3V3_A, ('J15', '4'): SPARE_3V3_A,
    dio('D2', 'A'): PICO_VSYS_A,                                   # LIO-226: the DNP VSYS diode, if fitted
    pico('VSYS'): PICO_VSYS_A,                                     # LIO-232: ... and the Pico's VSYS pin behind it (VSYS's tap tracks)
    imu('VCC'): IMU_A, **{(f'J{6 + i}', '1'): TOF_A for i in range(4)},
    drv('L', 'PMODE'): 0.0001, drv('R', 'PMODE'): 0.0001,          # DRV8874 PMODE: a logic input (uA)
    **{(r, '2'): 3.3 / 10e3 for r in ('R2', 'R4', 'R6', 'R8', 'R10', 'R18', 'R19', 'R20', 'R26')},   # 10 k pull-ups to 3V3 (I2C, ARM: LIO-226)
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#  - J1 (PB20, J1's pinout changed: J1_PINOUT): '+' at BAT+ (pin 2), '-' at GND (pin 1). B12a: the XT30 housing covers both pin ends
#    (J2 north, K1 south), so the marks sit beside the pins on the +u side, 0.4 mm off J1's silk outline; the footprint's own '+' / '-'
#    texts (past the housing ends, under J2 and K1) go to F.Fab (build_pcb).
#  - B12a (final review N2): '+' at pin 1 of both P03 terminals (U5A.1 VBAT_SW, U5B.1 5V: the screw nearer the robot centre line) and of
#    the Jetson 5 V header (J3.1). U5A.1's behind the terminal (its -u side) in the 1 mm slot between U5A's body and the end of J4's
#    pin row, south of J4's header body: inside J4's courtyard margin, off its body, pins and the C18 socket (pin row +- 7.62 mm), 0.6 mm
#    nearer U5A.1 than J4.6 (a 0.7 mm J4 move for room put J4 under the IMU module and its plug corridor into U2 / R3). U5B.1's past the
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#    edge so U5B's label fits beside it (SILK_LABEL_AT). J3.1's north of the Micro-Fit housing.
#  - LIO-242: a 'VIN' text (any mark but '+' / '-' is drawn as a SILK_TEXT_H text) at the DRV8874 carriers' VIN pin (U3P.1, U4P.1). The
#    Pololu 4035 is symmetric: turned 180 degrees it fits the same two sockets (carrier row L pin k in socket row P pin 8 - k), which puts
#    its VREF on VMOT and its GNDs on DRV_SLEEP / DRV_FAULT. The mark sits 2.1 mm past the carrier's pin-1 end (-v), off its body.
PIN_MARKS = {'J1': {J1_BAT_PIN[1]: '+', J1_GND_PIN[1]: '-'}, 'U5A': {'1': '+'}, 'U5B': {'1': '+'}, 'J3': {'1': '+'},
             'U3P': {str(DRV_PINS['VIN'][1]): 'VIN'}, 'U4P': {str(DRV_PINS['VIN'][1]): 'VIN'}}
PIN_MARK_AT = {'J1': {J1_BAT_PIN[1]: (3.5, 0.0), J1_GND_PIN[1]: (3.5, 0.0)}, 'U5A': {'1': (-5.85, -0.5)}, 'U5B': {'1': (2.0, 3.3)},
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# to right); the carrier zone starts at u 28; the tongue (u > 52.7) lies between the motor notches (v 16.6..83.4).
#  - band behind the carrier (u < 28, full height, exposed with the lid off): the rear-edge XH row J13 / J6 / J7 / J12 beside the Pico
#    (U1A u 8.8: its right socket's courtyard reaches u 28.38, ruling PB7), micro-USB out of the left edge; past the Pico's end the
#    VBAT_SW strip (v 52.3..57) joins J2.2 and the F2.1 pins and runs to the channel north of U3P; J2 / J1 on the rear edge, F2 beside
#    them (the VBAT_SW copper wraps its 2 x 2 F2.1 pins from both sides), F1, K1 (r 180: NO toward C1) and C1 on the VMOT bar to U4P.1,
#    J3 on the right edge (PB5 fallback; B12a: a right-angle Micro-Fit, its plug entering from beyond the right edge). The Pico-side pull-ups / pull-downs, the right encoder shifters, TP2 and R22 sit under the Pico.
#  - under the carrier (u >= 28, <= 16.27 mm): the drivers (both DRV8874 carriers turned 180 deg in place: logic rows U3L / U4L toward
#    the Pico at u 34.7 / 34.0, VIN/OUT/P rows U3P / U4P toward J4 / J5 at u 47.4 / 46.7, pin 1 at the low-v end; VIN on the VMOT bars),
#    the left encoder shifters Q1 / R1 / Q2 / R3 under the IMU module (outside both driver interiors; the relay driver Q5 / D1 / R9
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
